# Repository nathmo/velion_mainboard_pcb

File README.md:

# mainboard PCB
this repo contains the pcb file for the velion mainboard.
schematic + layout in PDF are available in the export folder
this board offer a control pannel with physical button for the use to control the seat + hand heater, a defroster, lightning (fog + interrior + warning), selenoid for a trunk latch, speed and mapping button.
it can drive a few load like the said heater and defroster, an aux load for music system, a USB-C port, rearview mirror with DRL and blinker
it also has input for a PAS, two brake switch and a seat sensor
it has an accelerometer for traction control
# TODO
add loadcell input if not seat sensor
add mosfet resitor input
add silkscreen +- 
break appart the control pannel from power mosftet
ombre chinoise issue with retro eclairage
add copper to block light, soldermask is not opaque enough

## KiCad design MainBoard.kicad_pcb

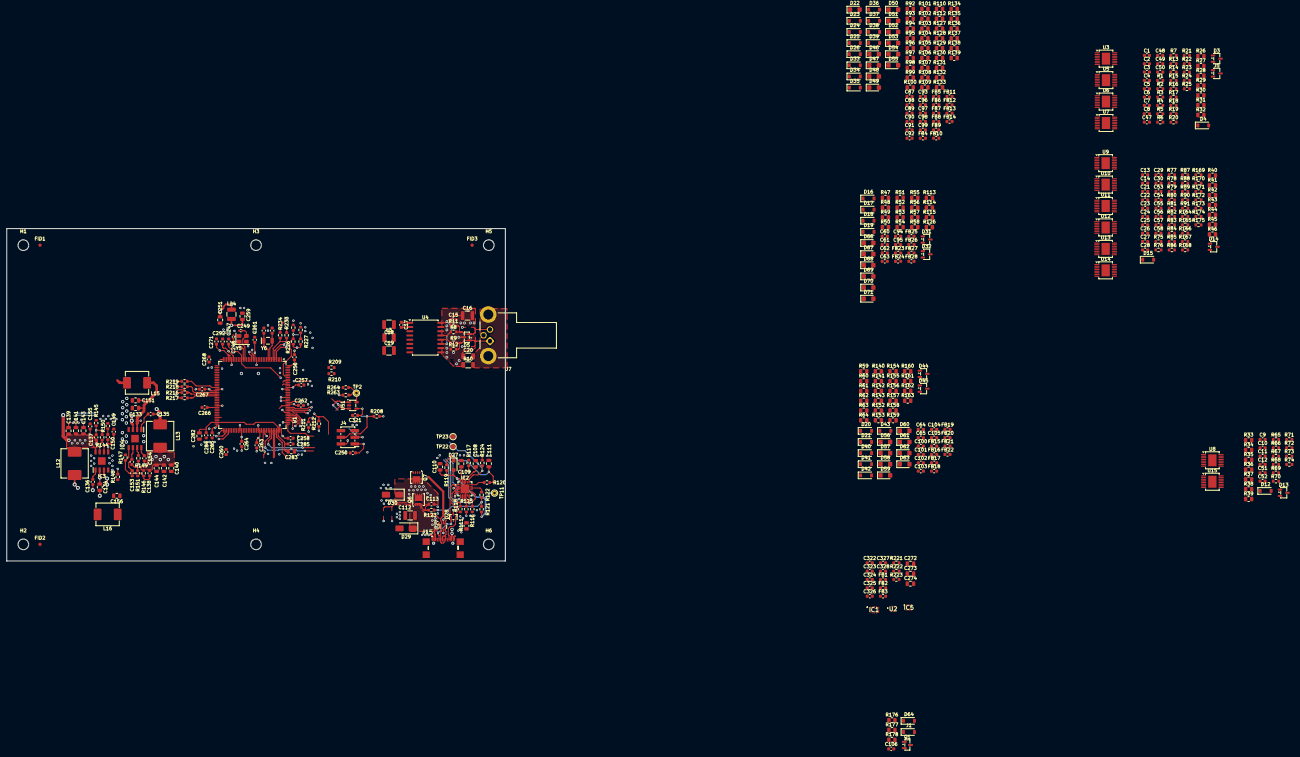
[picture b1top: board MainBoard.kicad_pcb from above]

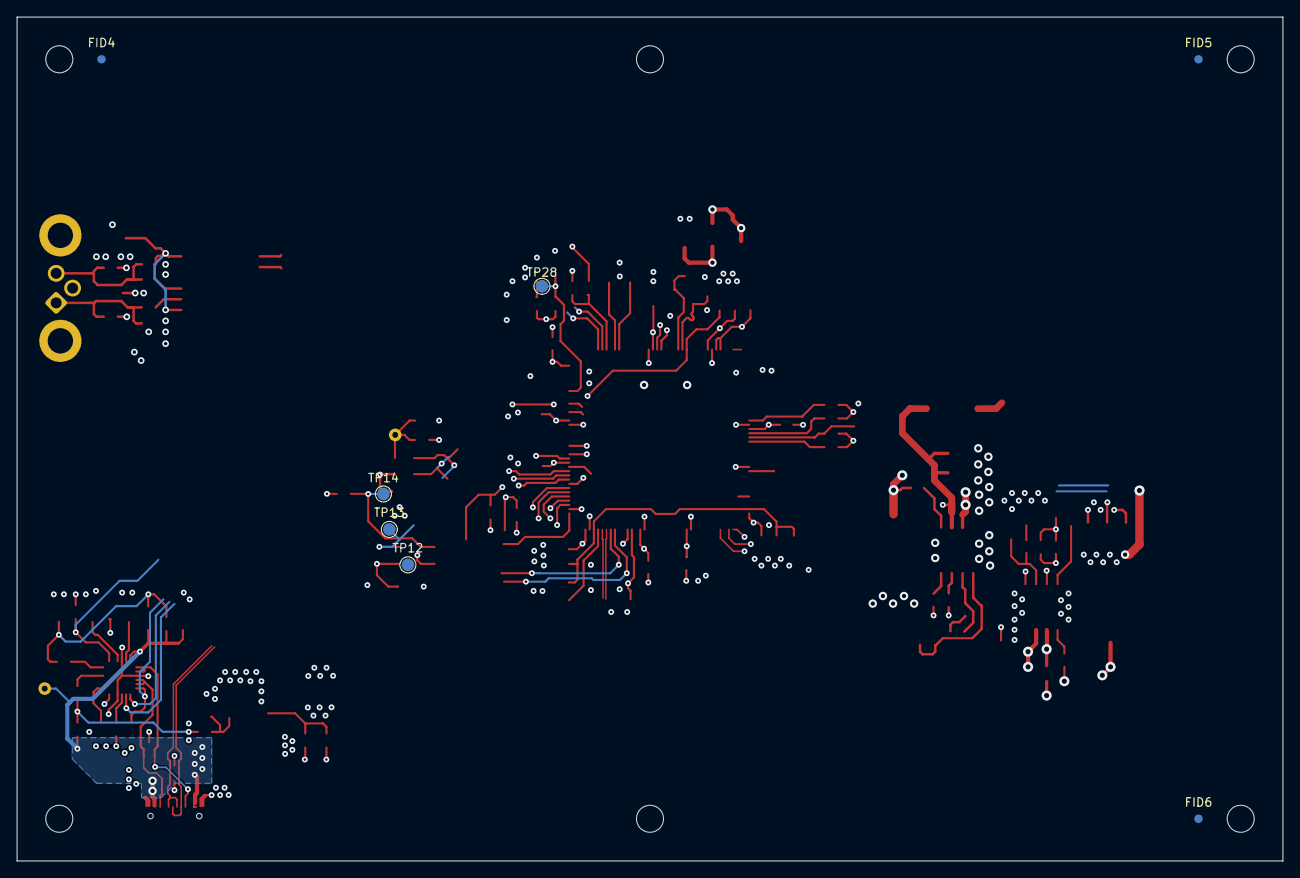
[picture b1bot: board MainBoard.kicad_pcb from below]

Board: 4 copper layers, 150.0 x 100.0 mm, 477 parts (7 on the bottom side), 247 nets.

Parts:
C1, C2, C3, C4, C5, C6, C7, C8, C9, C10, C11, C12, C13, C14, C21, C22, C23, C24, C25, C26, C27, C28, C29, C30: 1n; C_0603_1608Metric
C15, C17, C113, C155, C247, C250, C256, C257, C258, C260, C261, C262, C263, C264, C265, C266, C267, C268, C271, C284, C285, C292, C321, C322, C323, C324, C325, C326, C327: 0u1; C_0603_1608Metric
C16, C18, C19: 10u; C_1210_3225Metric
C20: 1n/1kV; C_1206_3216Metric
C47, C48, C49, C50, C51, C52, C53, C54, C55, C56, C57, C58, C60, C61, C62, C63, C64, C65, C94, C95, C104, C105: 100nF; C_0603_1608Metric
C87, C88, C89, C90, C91, C92, C93, C96, C97, C98, C99, C100, C101, C102, C103, C106: 470nF; C_0603_1608Metric
C108, C109, C110: 1u/16V/X7R; C_0805_2012Metric
C111: C; C_0805_2012Metric
C112: 4u7/X7R/50V; C_1210_3225Metric
C133, C134, C151, C156: 10u/25V/X5R; C_0805_2012Metric
C135, C136: 22n/X7R; C_0603_1608Metric
C137, C138, C149, C153: 100p; C_0603_1608Metric
C139, C140, C141, C142, C143, C144: 22u/16V/X7R; C_0805_2012Metric
C150, C152: 2n2; C_0603_1608Metric
C154, C328: 0u22; C_0603_1608Metric
C248, C249: 18p; C_0402_1005Metric
C251, C259, C272, C273, C274: 10u/16V/X7R; C_0805_2012Metric
C269, C270: 12p; C_0603_1608Metric
C282, C283: 2u2/16V/X7R; C_0805_2012Metric
D3, D13, D14, D31, D32, D44, D45: BAT54S_C7420333; SOT-23-3
D4, D12, D15, D16, D17, D18, D19, D20, D21, D23, D24, D25, D26, D33, D34, D35, D36, D37, D38, D39, D40, D41, D42, D43, D64: 1N4148W; D_SOD-123
D5: PESD2CAN; SOT-23
D22, D46, D47, D48, D49, D50, D51, D52, D53, D54, D55, D56, D57, D58, D63, D66, D67: SMF13A; D_SMF
D27: ??V/0.5W; D_SOD-123F
D28: ESDA25W; SOT-323_SC-70
D29, D30: P4SMAJ28A; D_SMA
D59, D60, D61, D62, D68, D69, D70, D71: SMF6V0A; D_SMF
FB1, FB2, FB3: FerriteBead_Small; L_0603_1608Metric
FB4, FB5, FB6, FB7, FB8, FB9, FB10, FB11, FB12, FB13, FB14, FB15, FB16, FB17, FB18, FB19, FB20, FB21, FB22, FB23, FB24, FB25, FB26, FB27, FB28: 100R; L_0603_1608Metric
FID1, FID2, FID3, FID4, FID5, FID6: Fiducial; Fiducial_1mm_Mask2mm
H1, H2, H3, H4, H5, H6: MountingHole; MountingHole_3.2mm_M3
IC1: ASM330LHHTR; LSM6DS3USTR
IC2: STUSB4500LQTR; QFN-24-1EP_4x4mm_P0.5mm_EP2.7x2.7mm
IC3, IC4: RT8293BHZSP; SOIC127P600X175-9N
IC5: IIS2MDCTR
J1: Conn_01x04; D_SOD-123
J4: Conn_01x06_Pin; PinHeader_2x03_P2.00mm_Vertical_SMD
J5: Conn_01x09; SOT-23-3
J7: IEC61076-2_M8_B-coding_01x03_Plug_Shielded; Amphenol_M8S-03PMMR-SF8001
J15: USB_C_2.0; USB_C_Receptacle_GCT_USB4110-GF-A
L3: L_Ferrite; L_1210_3225Metric
L12: 6u8/5A; L_APV_APH0850
L13: 4u7/5A; L_APV_APH0850
L15, L16: 1u/5A; L_APV_APH0650
L24: 10u/450mA; L_1210_3225Metric
Q1: DTC123Y; SOT-23
Q6, Q7: STL9P3LLH6; Diodes_PowerDI3333-8
R1, R2, R3, R4, R5, R6, R7, R13, R14, R15, R16, R17, R69, R70, R71, R72, R73, R74, R87, R88, R89, R90, R91, R120, R125, R164, R165, R166, R167, R168, R169, R170, R171, R172, R173, R174, R175: 1k; R_0603_1608Metric
R8, R9: 10R; R_0603_1608Metric
R10: 1M; R_1206_3216Metric
R11, R12, R118, R208: 10k; R_0603_1608Metric
R18, R19, R20, R21, R22, R23, R24, R25, R65, R66, R67, R68, R75, R76, R77, R78, R79, R80, R81, R82, R83, R84, R85, R86: 22R; R_0603_1608Metric
R26, R27, R28, R29, R30, R31, R34, R35, R36, R37, R38, R39, R40, R41, R42, R43, R44, R45: 1kΩ; R_0805_2012Metric
R32, R33, R46, R47, R50, R57, R58, R63, R64: 4.7kΩ; R_0805_2012Metric
R48, R51, R55, R56, R61, R62, R94, R95, R98, R101, R104, R107, R110, R113, R115, R128, R131, R134, R137, R140, R143, R154, R157, R160, R162, R176: 10kΩ; R_0805_2012Metric
R49, R52, R53, R54, R59, R60: 20kΩ; R_0805_2012Metric
R92, R97, R100, R103, R106, R109, R127, R130, R133, R136, R139, R142, R153, R156, R159, R178: 1.2kΩ; R_0805_2012Metric
R93, R96, R99, R102, R105, R108, R112, R129, R132, R135, R138, R141, R152, R155, R158, R177: 33kΩ; R_0805_2012Metric
R111: 1M; R_0805_2012Metric
R114, R126, R161, R163: 15kΩ; R_0805_2012Metric
R116, R117, R121, R148, R149: 100k; R_0603_1608Metric
R119: 470R; R_0603_1608Metric
R122, R151: 22k; R_0603_1608Metric
R123: 100; R_0603_1608Metric
R124: 4k7; R_0603_1608Metric
R144: 62k; R_0603_1608Metric
R145: 11k8; R_0603_1608Metric
R146: 75k; R_0603_1608Metric
R147: 24k; R_0603_1608Metric
R150: 33k; R_0603_1608Metric
R209, R210, R211, R212, R216, R217, R218, R219, R221, R263, R264: 2k2; R_0603_1608Metric
R220, R222, R223, R226, R227, R228, R233, R234: 0R; R_0603_1608Metric
TP2: MEM_WP; TestPoint_THTPad_D1.5mm_Drill0.7mm
TP11: VBUS_USB; TestPoint_THTPad_D1.5mm_Drill0.7mm
TP12: SWCLK; TestPoint_Pad_D1.5mm
TP13: SWDIO; TestPoint_Pad_D1.5mm
TP14: ~{ucRST}; TestPoint_Pad_D1.5mm
TP22: I2C2.SCK; TestPoint_Pad_D1.5mm
TP23: I2C2.DATA; TestPoint_Pad_D1.5mm
TP28: BOOT; TestPoint_Pad_D1.5mm
U1: STM32H723ZGT6; LQFP-144_20x20mm_P0.5mm
U2: BMP581
U3, U5, U6, U7, U8, U9, U10, U11, U12, U13, U14, U15: VND7050AJTR; PowerSSO-16-1EP_3.9x4.9mm_P0.5mm_EP2.5x3.61mm
U4: CA-IS2062W; SOIC-16W_7.5x10.3mm_P1.27mm
U27: USBLC6-2P6; SOT-666
U51: 24AA02-OT; SOT-23-5
Y5: 12M; Crystal_SMD_Abracon_ABM8G-4Pin_3.2x2.5mm
Y6: 32,768kHz; Crystal_SMD_EuroQuartz_EQ161-2Pin_3.2x1.5mm

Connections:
+3.3V: C19.1, C138.1, C140.1, C142.1, C144.1, C250.1, C251.1, C256.1, C257.1, C258.1, C261.1, C262.1, C263.1, C264.1, C265.1, C266.1, C267.1, C268.1, C292.1, C321.1, C322.1, C323.1, C324.1, D3.2 (K2), D13.2 (K2), D14.2 (K2), D16.1, D17.1, D18.1, D19.1, D20.1, D21.1, D23.1, D24.1, D25.1, D26.1, D31.2 (K2), D32.2 (K2), D33.1, D34.1, D35.1, D36.1, D37.1, D38.1, D39.1, D40.1, D41.1, D42.1, D43.1, D44.2 (K2), D45.2 (K2), D64.1, FB1.2, FB2.2, FB3.2, IC1.5 (VDDIO), IC1.12 (CS), IC5.3 (CS), IC5.10 (VDD_IO), J4.1, L3.1, L13.2, L24.1, R26.2, R34.2, R40.2, R124.1, R146.1, R208.1, R209.1, R210.1, R211.1, R212.1, R216.1, R217.1, R218.1, R219.1, R221.1, R222.1, R226.1, R227.1, R233.2, R263.1, U1.17 (VDD), U1.30 (VDD), U1.39 (VDD), U1.52 (VDD), U1.62 (VDD), U1.72 (VDD), U1.84 (VDD), U1.95 (VDD33USB), U1.108 (VDD), U1.121 (VDD), U1.131 (VDD), U1.144 (VDD), U2.1 (VDDIO), U51.4 (V_{CC})
+3.3VA: C259.1, C260.1, C271.1, L24.2, U1.32 (VREF+), U1.33 (VDDA)
+5V: C137.1, C139.1, C141.1, C143.1, D30.1 (A1), L12.2, Q7.1 (S), Q7.2 (S), Q7.3 (S), R47.1, R50.1, R57.1, R58.1, R63.1, R64.1, R144.1, U27.5 (VBUS)
+12V: C47.1, C48.1, C49.1, C50.1, C51.1, C52.1, C53.1, C54.1, C55.1, C56.1, C57.1, C58.1, L15.2, L16.2, R92.1, R97.1, R100.1, R103.1, R106.1, R109.1, R127.1, R130.1, R133.1, R136.1, R139.1, R142.1, R153.1, R156.1, R159.1, R178.1, U3.17 (VCC), U5.17 (VCC), U6.17 (VCC), U7.17 (VCC), U8.17 (VCC), U9.17 (VCC), U10.17 (VCC), U11.17 (VCC), U12.17 (VCC), U13.17 (VCC), U14.17 (VCC), U15.17 (VCC)
/BackLightsControl/CargoCompLampOUT: R84.1, U9.13 (OUTPUT0), U9.14 (OUTPUT0), U9.15 (OUTPUT0), U9.16 (OUTPUT0)
/BackLightsControl/RearDirLampLeftOUT: R86.1, U10.13 (OUTPUT0), U10.14 (OUTPUT0), U10.15 (OUTPUT0), U10.16 (OUTPUT0)
/BackLightsControl/RearDirLampRightOUT: R83.1, U9.9 (OUTPUT1), U9.10 (OUTPUT1), U9.11 (OUTPUT1), U9.12 (OUTPUT1)
/BackLightsControl/RearFogLampOUT: R75.1, U11.9 (OUTPUT1), U11.10 (OUTPUT1), U11.11 (OUTPUT1), U11.12 (OUTPUT1)
/BackLightsControl/RearPosLampOUT: R76.1, U11.13 (OUTPUT0), U11.14 (OUTPUT0), U11.15 (OUTPUT0), U11.16 (OUTPUT0)
/BackLightsControl/RearSense: D14.3 (A), R44.1
/BackLightsControl/Reserved2OUT: R80.1, U13.13 (OUTPUT0), U13.14 (OUTPUT0), U13.15 (OUTPUT0), U13.16 (OUTPUT0)
/BackLightsControl/ReversingLampOUT: R78.1, U12.13 (OUTPUT0), U12.14 (OUTPUT0), U12.15 (OUTPUT0), U12.16 (OUTPUT0)
/BackLightsControl/Rezerved1OUT: R77.1, U12.9 (OUTPUT1), U12.10 (OUTPUT1), U12.11 (OUTPUT1), U12.12 (OUTPUT1)
/BackLightsControl/StopLampOUT: R85.1, U10.9 (OUTPUT1), U10.10 (OUTPUT1), U10.11 (OUTPUT1), U10.12 (OUTPUT1)
/BackLightsControl/TT-DirIndLeftOUT: R79.1, U13.9 (OUTPUT1), U13.10 (OUTPUT1), U13.11 (OUTPUT1), U13.12 (OUTPUT1)
/BackLightsControl/TT-DirIndRightOUT: R81.1, U14.9 (OUTPUT1), U14.10 (OUTPUT1), U14.11 (OUTPUT1), U14.12 (OUTPUT1)
/BackLightsControl/TT-DrivingBeamOUT: R82.1, U14.13 (OUTPUT0), U14.14 (OUTPUT0), U14.15 (OUTPUT0), U14.16 (OUTPUT0)
/BackLightsControl/~FaultRST: R26.1, R27.1, R34.1, R35.1, R40.1, R41.1
/FrontLightsControl/AudibleWarnOUT: R25.1, U7.13 (OUTPUT0), U7.14 (OUTPUT0), U7.15 (OUTPUT0), U7.16 (OUTPUT0)
/FrontLightsControl/DaytimeLampOUT: R22.1, U6.9 (OUTPUT1), U6.10 (OUTPUT1), U6.11 (OUTPUT1), U6.12 (OUTPUT1)
/FrontLightsControl/DrivingBeamLampOUT: R23.1, U6.13 (OUTPUT0), U6.14 (OUTPUT0), U6.15 (OUTPUT0), U6.16 (OUTPUT0)
/FrontLightsControl/FrontDirLampLeftOUT: R21.1, U5.13 (OUTPUT0), U5.14 (OUTPUT0), U5.15 (OUTPUT0), U5.16 (OUTPUT0)
/FrontLightsControl/FrontDirLampRightOUT: J5.3, R18.1, U3.9 (OUTPUT1), U3.10 (OUTPUT1), U3.11 (OUTPUT1), U3.12 (OUTPUT1)
/FrontLightsControl/FrontPosLampOUT: J5.2, R19.1, U3.13 (OUTPUT0), U3.14 (OUTPUT0), U3.15 (OUTPUT0), U3.16 (OUTPUT0)
/FrontLightsControl/FrontSense: D3.3 (A), R30.1
/FrontLightsControl/PassingBeamLampOUT: R20.1, U5.9 (OUTPUT1), U5.10 (OUTPUT1), U5.11 (OUTPUT1), U5.12 (OUTPUT1)
/FrontLightsControl/Reserved3OUT: R24.1, U7.9 (OUTPUT1), U7.10 (OUTPUT1), U7.11 (OUTPUT1), U7.12 (OUTPUT1)
/HumanInterfaceCircuits/AcousticWarnSW: C89.1, D25.2, R98.1, R99.2
/HumanInterfaceCircuits/Assist+SW: C97.1, D37.2, R131.1, R132.2
/HumanInterfaceCircuits/Assist+SW_IN: D53.1 (A1), FB10.2
/HumanInterfaceCircuits/Assist-SW: C98.1, D38.2, R134.1, R135.2
/HumanInterfaceCircuits/Assist-SW_IN: D55.1 (A1), FB14.2
/HumanInterfaceCircuits/DirIndSW_L: C87.1, D23.2, R93.2, R94.1
/HumanInterfaceCircuits/DirIndSW_R: C88.1, D24.2, R95.1, R96.2
/HumanInterfaceCircuits/ForwardSW: C96.1, D36.2, R128.1, R129.2
/HumanInterfaceCircuits/ForwardSW_IN: D52.1 (A1), FB9.2
/HumanInterfaceCircuits/LightChangeSW: C90.1, D26.2, R101.1, R102.2
/HumanInterfaceCircuits/LightChangeSW_IN: D48.1 (A1), FB7.2
/HumanInterfaceCircuits/MappingSW: C91.1, D33.2, R104.1, R105.2
/HumanInterfaceCircuits/MappingSW_IN: D49.1 (A1), FB11.2
/HumanInterfaceCircuits/ReverseSW: C93.1, D35.2, R110.1, R112.2
/HumanInterfaceCircuits/ReverseSW_IN: D51.1 (A1), FB13.2
/HumanInterfaceCircuits/SpeedLimSW: C92.1, D34.2, R107.1, R108.2
/HumanInterfaceCircuits/SpeedLimSW_IN: D50.1 (A1), FB12.2
/HumanInterfaceCircuits/VehicleStartSW: C99.1, D39.2, R137.1, R138.2
/HumanInterfaceCircuits/VehicleStartSW_IN: D54.1 (A1), FB8.2
/HumanInterfaceCircuitsII/ACCELERATOR_AN: C104.1, D44.3 (A), R160.2, R161.1
/HumanInterfaceCircuitsII/BreakLeft_SW: C102.1, D42.2, R154.1, R155.2
/HumanInterfaceCircuitsII/BreakRight_SW: C103.1, D43.2, R157.1, R158.2
/HumanInterfaceCircuitsII/PAS_A: C64.1, D20.2, R59.1, R61.2
/HumanInterfaceCircuitsII/PAS_B: C65.1, D21.2, R60.1, R62.2
/HumanInterfaceCircuitsII/REGEN_AN: C105.1, D45.3 (A), R162.2, R163.1
/HumanInterfaceCircuitsII/Seat_SW: C101.1, D41.2, R143.1, R152.2
/HumanInterfaceCircuitsII/Trunk_SW: C100.1, D40.2, R140.1, R141.2
/IMU/~INT_ACC: IC1.4 (INT1), R221.2
/MCU/AUX_AN: C95.1, D32.3 (A), R115.2, R126.1
/MCU/AUX_PAS_A: C62.1, D18.2, R53.1, R55.2
/MCU/AUX_PAS_B: C63.1, D19.2, R54.1, R56.2
/MCU/FogLight_SW: C106.1, D64.2, R176.1, R177.2
/MCU/I2C1.CLK: IC1.13 (SCL), IC5.1 (SCL/SPC), R209.2, U2.2 (SCK)
/MCU/I2C1.DATA: IC1.14 (SDA), IC5.4 (SDA/SDI/SDO), R210.2, U2.4 (SDI), U2.5 (SDO)
/MCU/I2C2.DATA: IC2.8 (SDA), R212.2, TP23.1 (1_1), U51.1 (SCL)
/MCU/I2C2.SCK: IC2.7 (SCL), R211.2, TP22.1 (1_1), U51.3 (SDA)
/MCU/SW0.SWCLK: J4.2, TP12.1 (1_1), U1.109 (PA14(JTCK)
/MCU/SW0.SWDIO: J4.3, TP13.1 (1_1), U1.105 (PA13(JTMS)
/MCU/SW0.~ucRST: C247.1, J4.4, R208.2, TP14.1 (1_1), U1.25 (NRST)
/MCU/SideSense: D13.3 (A), R38.1
/MCU/TORQUE_AN: C94.1, D31.3 (A), R113.2, R114.1
/MCU/TORQUE_PAS_A: C60.1, D16.2, R48.2, R49.1
/MCU/TORQUE_PAS_B: C61.1, D17.2, R51.2, R52.1
/MCU/USB_N: J15.A7 (D-), J15.B7 (D-), U27.3 (I/O2), U27.4 (I/O2)
/MCU/USB_P: J15.A6 (D+), J15.B6 (D+), U27.1 (I/O1), U27.6 (I/O1)
/MCU/USB_PD_ALERT: IC2.19 (ALERT), R124.2
/MCU/USB_PD_RST: IC2.6 (RESET), R118.1
/PowertrainInterface/CAN_SH: C20.2, J7.SH, R10.2
/SideIndicatorLightsControl/SideDirLampLeftOUT: R67.1, U15.9 (OUTPUT1), U15.10 (OUTPUT1), U15.11 (OUTPUT1), U15.12 (OUTPUT1)
/SideIndicatorLightsControl/SideDirLampRightOUT: R65.1, U8.9 (OUTPUT1), U8.10 (OUTPUT1), U8.11 (OUTPUT1), U8.12 (OUTPUT1)
/SideIndicatorLightsControl/SideMarkLampLeftOUT: R68.1, U15.13 (OUTPUT0), U15.14 (OUTPUT0), U15.15 (OUTPUT0), U15.16 (OUTPUT0)
/SideIndicatorLightsControl/SideMarkLampRightOUT: R66.1, U8.13 (OUTPUT0), U8.14 (OUTPUT0), U8.15 (OUTPUT0), U8.16 (OUTPUT0)
/USB_PD/CC1_USB: D28.1 (K), IC2.1 (CC1DB), IC2.2 (CC1), J15.A5 (CC1)
/USB_PD/CC2_USB: D28.2 (K), IC2.4 (CC2), IC2.5 (CC2DB), J15.B5 (CC2)
/USB_PD/SHD_USB: J15.S1 (SHIELD), R111.2
/USB_PD/VBUS_SYS: C113.1, Q6.5 (D), Q7.5 (D), R125.2
/USB_PD/VBUS_USB: C110.1, C112.1, D27.2 (A), D29.1 (A1), IC2.24 (VDD), J15.A4 (VBUS), J15.A9 (VBUS), J15.B4 (VBUS), J15.B9 (VBUS), Q6.1 (S), Q6.2 (S), Q6.3 (S), R119.1, R121.1, TP11.1 (1_1)
GND: C1.2, C2.2, C3.2, C4.2, C5.2, C6.2, C7.2, C8.2, C9.2, C10.2, C11.2, C12.2, C13.2, C14.2, C17.2, C18.2, C19.2, C21.2, C22.2, C23.2, C24.2, C25.2, C26.2, C27.2, C28.2, C29.2, C30.2, C47.2, C48.2, C49.2, C50.2, C51.2, C52.2, C53.2, C54.2, C55.2, C56.2, C57.2, C58.2, C60.2, C61.2, C62.2, C63.2, C64.2, C65.2, C87.2, C88.2, C89.2, C90.2, C91.2, C92.2, C93.2, C94.2, C95.2, C96.2, C97.2, C98.2, C99.2, C100.2, C101.2, C102.2, C103.2, C104.2, C105.2, C106.2, C108.2, C109.2, C110.2, C111.2, C112.2, C133.2, C134.2, C139.2, C140.2, C141.2, C142.2, C143.2, C144.2, C149.1, C151.2, C153.1, C154.1, C155.1, C156.2, C247.2, C248.2, C249.2, C250.2, C251.2, C256.2, C257.2, C258.2, C259.2, C260.2, C261.2, C262.2, C263.2, C264.2, C265.2, C266.2, C267.2, C268.2, C269.2, C270.2, C271.2, C272.2, C273.2, C274.2, C282.2, C283.2, C284.2, C285.2, C292.2, C321.2, C322.2, C323.2, C324.2, C325.2, C326.2, C327.2, C328.2, D3.1 (K1), D4.1, D12.1, D13.1 (K1), D14.1 (K1), D15.1, D22.2 (A2), D28.3 (A), D29.2 (A2), D30.2 (A2), D31.1 (K1), D32.1 (K1), D44.1 (K1), D45.1 (K1), D46.2 (A2), D47.2 (A2), D48.2 (A2), D49.2 (A2), D50.2 (A2), D51.2 (A2), D52.2 (A2), D53.2 (A2), D54.2 (A2), D55.2 (A2), D56.2 (A2), D57.2 (A2), D58.2 (A2), D59.2 (A2), D60.2 (A2), D61.2 (A2), D62.2 (A2), D63.2 (A2), D66.2 (A2), D67.2 (A2), D68.2 (A2), D69.2 (A2), D70.2 (A2), D71.2 (A2), IC1.1 (SDO/SA0), IC1.6 (GND), IC1.7 (GND), IC2.3 (NU), IC2.10 (GND), IC2.22 (VSYS), IC2.25 (EP), IC3.4 (GND), IC3.9 (EP), IC4.4 (GND), IC4.9 (EP), IC5.6 (GND), IC5.8 (GND), J1.2, J4.5, J5.1, J15.A1 (GND), J15.A12 (GND), J15.B1 (GND), J15.B12 (GND), Q1.2 (E), R31.2, R32.2, R33.2, R39.2, R45.2, R46.2, R49.2, R52.2, R53.2, R54.2, R59.2, R60.2, R94.2, R95.2, R98.2, R101.2, R104.2, R107.2, R110.2, R111.1, R114.2, R116.2, R117.2, R118.2, R126.2, R128.2, R131.2, R134.2, R137.2, R140.2, R143.2, R145.2, R147.2, R150.2, R151.2, R154.2, R157.2, R161.2, R163.2, R176.2, R220.1, R223.2, R228.1, R264.2, U1.16 (VSS), U1.31 (VSSA), U1.38 (VSS), U1.51 (VSS), U1.61 (VSS), U1.83 (VSS), U1.94 (VSS), U1.107 (VSS), U1.120 (VSS), U1.130 (VSS), U2.3 (GND), U2.8 (GND), U2.9 (GND), U4.2 (GNDA), U4.8 (GNDA), U27.2 (GND), U51.2 (V_{SS}), Y5.2, Y5.4
GND1: C15.2, C16.2, C20.1, D5.3 (common), J7.2, R10.1, R12.1, U4.9 (GNDB), U4.10 (GNDB), U4.15 (GNDB)
unnamed: C1.1, R18.2
unnamed: C2.1, R19.2
unnamed: C3.1, R20.2
unnamed: C4.1, R21.2
unnamed: C5.1, R22.2
unnamed: C6.1, R23.2
unnamed: C7.1, R24.2
unnamed: C8.1, R25.2
unnamed: C9.1, R65.2
unnamed: C10.1, R66.2
unnamed: C11.1, R67.2
unnamed: C12.1, R68.2
unnamed: C13.1, R75.2
unnamed: C14.1, R76.2
unnamed: C15.1, C16.1, R11.1, U4.11 (Viso), U4.16 (Viso)
unnamed: C21.1, R77.2
unnamed: C22.1, R78.2
unnamed: C23.1, R79.2
unnamed: C24.1, R80.2
unnamed: C25.1, R81.2
unnamed: C26.1, R82.2
unnamed: C27.1, R83.2
unnamed: C28.1, R84.2
unnamed: C29.1, R85.2
unnamed: C30.1, R86.2
unnamed: C150.1, R150.1
unnamed: C152.1, R151.1
unnamed: C282.1, C283.1, C284.1, C285.1, U1.71 (VCAP), U1.106 (VCAP)
unnamed: D5.1 (A1), J7.1, R9.2, R12.2
unnamed: D5.2 (A2), J7.3, R8.2, R11.2
unnamed: D22.1 (A1), FB5.1, R99.1, R100.2
unnamed: C111.1, D27.1 (K), R119.2, R120.1
unnamed: D46.1 (A1), FB6.1, R96.1, R97.2
unnamed: D47.1 (A1), FB4.1, R92.2, R93.1
unnamed: D56.1 (A1), FB15.2
unnamed: D57.1 (A1), FB16.2
unnamed: D58.1 (A1), FB18.2
unnamed: D59.1 (A1), FB19.2
unnamed: D60.1 (A1), FB20.2
unnamed: D61.1 (A1), FB21.2
unnamed: D62.1 (A1), FB22.2
unnamed: D63.1 (A1), FB17.2
unnamed: D66.1 (A1), FB23.2
unnamed: D67.1 (A1), FB28.2
unnamed: D68.1 (A1), FB26.2
unnamed: D69.1 (A1), FB27.2
unnamed: D70.1 (A1), FB24.2
unnamed: D71.1 (A1), FB25.2
unnamed: FB7.1, R102.1, R103.2
unnamed: FB8.1, R138.1, R139.2
unnamed: FB9.1, R129.1, R130.2
unnamed: FB10.1, R132.1, R133.2
unnamed: FB11.1, R105.1, R106.2
unnamed: FB12.1, R108.1, R109.2
unnamed: FB13.1, R112.1, R127.2
unnamed: FB14.1, R135.1, R136.2
unnamed: FB15.1, R141.1, R142.2
unnamed: FB16.1, R152.1, R153.2
unnamed: FB17.1, R158.1, R159.2
unnamed: FB18.1, R155.1, R156.2
unnamed: FB19.1, R61.1, R63.2
unnamed: FB20.1, R62.1, R64.2
unnamed: FB21.1, R160.1
unnamed: FB22.1, R162.1
unnamed: FB23.1, R113.1
unnamed: FB24.1, R50.2, R51.1
unnamed: FB25.1, R47.2, R48.1
unnamed: FB26.1, R55.1, R57.2
unnamed: FB27.1, R56.1, R58.2
unnamed: FB28.1, R115.1
unnamed: IC1.10 (NC_1), IC1.11 (NC_2)
unnamed: C274.1, C325.1, FB3.1, IC1.8 (VDD)
unnamed: IC2.12 (ADDR0), R117.1
unnamed: IC2.13 (ADDR1), R116.1
unnamed: IC2.9 (DISCH), R125.1
unnamed: IC2.16 (VBUS_EN_SNK), R122.2
unnamed: IC2.18 (VBUS_VS_DISCH), R120.2
unnamed: C108.1, IC2.21 (VREG_1V2)
unnamed: C109.1, IC2.23 (VREG_2V7)
unnamed: C136.1, IC3.1 (BOOT)
unnamed: C149.2, C150.2, IC3.6 (COMP)
unnamed: IC3.7 (EN), R148.2
unnamed: C137.2, IC3.5 (FB), R144.2, R145.1
unnamed: C155.2, IC3.8 (SS)
unnamed: C136.2, IC3.3 (SW), L12.1
unnamed: C134.1, C156.1, IC3.2 (VIN), L16.1, R148.1
unnamed: C135.1, IC4.1 (BOOT)
unnamed: C152.2, C153.2, IC4.6 (COMP)
unnamed: IC4.7 (EN), R149.2
unnamed: C138.2, IC4.5 (FB), R146.2, R147.1
unnamed: C154.2, IC4.8 (SS)
unnamed: C135.2, IC4.3 (SW), L13.1
unnamed: C133.1, C151.1, IC4.2 (VIN), L15.1, R149.1
unnamed: C328.1, IC5.5 (C1)
unnamed: C273.1, C326.1, FB2.1, IC5.9 (VDD)
unnamed: J1.1, R177.1, R178.2
unnamed: C113.2, Q6.4 (G), Q7.4 (G), R123.2
unnamed: R121.2, R122.1, R123.1
unnamed: R220.2, R226.2, TP28.1 (1_1), U1.138 (BOOT0)
unnamed: R227.2, R228.2, U1.143 (PDR_ON)
unnamed: R233.1, R234.2, U1.6 (VBAT)
unnamed: C270.1, U1.8 (PC14)
unnamed: C269.1, U1.9 (PC15), Y6.1 (1_1)
unnamed: C249.1, U1.23 (PH0), Y5.3
unnamed: C248.1, U1.24 (PH1), Y5.1
unnamed: R222.2, R223.1, U2.6 (CSB)
unnamed: C272.1, C327.1, FB1.1, U2.10 (VDD)
unnamed: D4.2, R32.1, U3.4 (GND), U5.4 (GND), U6.4 (GND), U7.4 (GND)
unnamed: R1.2, U3.1 (INPUT0)
unnamed: R3.2, U3.8 (INPUT1)
unnamed: R30.2, R31.1, U3.7 (MultiSense), U5.7 (MultiSense), U6.7 (MultiSense), U7.7 (MultiSense)
unnamed: R28.2, U3.5 (SEL0), U5.5 (SEL0), U6.5 (SEL0), U7.5 (SEL0)
unnamed: R29.2, U3.6 (SEL1), U5.6 (SEL1), U6.6 (SEL1), U7.6 (SEL1)
unnamed: R2.2, U3.3 (SEn)
unnamed: R27.2, U3.2 (~FaultRST), U5.2 (~FaultRST), U6.2 (~FaultRST), U7.2 (~FaultRST)
unnamed: R8.1, U4.13 (H)
unnamed: R9.1, U4.12 (L)
unnamed: C17.1, C18.1, L3.2, U4.1 (Vcc)
unnamed: R4.2, U5.1 (INPUT0)
unnamed: R5.2, U5.8 (INPUT1)
unnamed: R6.2, U5.3 (SEn)
unnamed: R7.2, U6.1 (INPUT0)
unnamed: R13.2, U6.8 (INPUT1)
unnamed: R14.2, U6.3 (SEn)
unnamed: R15.2, U7.1 (INPUT0)
unnamed: R16.2, U7.8 (INPUT1)
unnamed: R17.2, U7.3 (SEn)
unnamed: R69.2, U8.1 (INPUT0)
unnamed: R70.2, U8.8 (INPUT1)
unnamed: R71.2, U8.3 (SEn)
unnamed: R87.2, U9.1 (INPUT0)
unnamed: R88.2, U9.8 (INPUT1)
unnamed: R89.2, U9.3 (SEn)
unnamed: D15.2, R46.1, U9.4 (GND), U10.4 (GND), U11.4 (GND), U12.4 (GND), U13.4 (GND), U14.4 (GND)
unnamed: R90.2, U10.1 (INPUT0)
unnamed: R91.2, U10.8 (INPUT1)
unnamed: R44.2, R45.1, U9.7 (MultiSense), U10.7 (MultiSense), U11.7 (MultiSense), U12.7 (MultiSense), U13.7 (MultiSense), U14.7 (MultiSense)
unnamed: R42.2, U9.5 (SEL0), U10.5 (SEL0), U11.5 (SEL0), U12.5 (SEL0), U13.5 (SEL0), U14.5 (SEL0)
unnamed: R43.2, U9.6 (SEL1), U10.6 (SEL1), U11.6 (SEL1), U12.6 (SEL1), U13.6 (SEL1), U14.6 (SEL1)
unnamed: R164.2, U10.3 (SEn)
unnamed: R41.2, U9.2 (~FaultRST), U10.2 (~FaultRST), U11.2 (~FaultRST), U12.2 (~FaultRST), U13.2 (~FaultRST), U14.2 (~FaultRST)
unnamed: R165.2, U11.1 (INPUT0)
unnamed: R167.2, U11.8 (INPUT1)
unnamed: R166.2, U11.3 (SEn)
unnamed: R168.2, U12.1 (INPUT0)
unnamed: R169.2, U12.3 (SEn)
unnamed: R170.2, U13.1 (INPUT0)
unnamed: R172.2, U13.8 (INPUT1)
unnamed: R171.2, U13.3 (SEn)
unnamed: R173.2, U14.1 (INPUT0)
unnamed: R175.2, U14.8 (INPUT1)
unnamed: R174.2, U14.3 (SEn)
unnamed: D12.2, R33.1, U8.4 (GND), U15.4 (GND)
unnamed: R72.2, U15.1 (INPUT0)
unnamed: R73.2, U15.8 (INPUT1)
unnamed: R38.2, R39.1, U8.7 (MultiSense), U15.7 (MultiSense)
unnamed: R36.2, U8.5 (SEL0), U15.5 (SEL0)
unnamed: R37.2, U8.6 (SEL1), U15.6 (SEL1)
unnamed: R74.2, U15.3 (SEn)
unnamed: R35.2, U8.2 (~FaultRST), U15.2 (~FaultRST)
unnamed: R263.2, R264.1, TP2.1 (1_1), U51.5 (WP)

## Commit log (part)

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2025-12-16 added current status of PCB
2025-12-16 Auto-export KiCad PDFs
2025-12-17 changed a connector
2025-12-19 reorganized sheeet
2025-12-19 schematic done, only INA228 left to size
2025-12-22 BOM done, pcb layout done, routing ...
2025-12-22 routed a few more track
2025-12-23 routing
2025-12-23 PCB ready for fab
2025-12-23 ready for forder
2025-12-26 added POWER signal for siliXcon
2025-12-26 added 120 R CAN terminator
2025-12-26 regenerated zip for Order
2026-02-13 Create README.md for mainboard PCB project
    Add initial README with project details and TODOs
2026-03-16 added BOM
